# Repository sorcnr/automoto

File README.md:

# AutoMoto — Akıllı Motosiklet Telemetri, Güvenlik ve Keyless Go Sistemi

AutoMoto; ESP32-S3 mimarisi, SIMCom SIM808 GSM/GPRS + GPS hücresel modülü, BLE 5.0 yakınlık algılaması (Keyless Go) ve otomotiv sınıfı katı-hal (`PROFET` / `SSR`) anahtarlama teknolojisine dayanan yeni nesil bir akıllı motosiklet telemetri ve güvenlik platformudur.

## Proje ve Tasarım Dokümantasyonu

* **Proje Genel Tanımı ve Sistem Mimarisi:** [PROJECT.md](file:///home/sorcnr/Documents/automoto/PROJECT.md)
* **PCB & Şematik Teknik İmalat Şartnamesi (v4.0):** [hardware/pcb/PCB_SPECIFICATION.md](file:///home/sorcnr/Documents/automoto/hardware/pcb/PCB_SPECIFICATION.md)

---

## Donanım ve CAD Dosyaları (`hardware/pcb/`)

* **KiCad 10 Elektrik Şematik:** [hardware/pcb/automoto.kicad_sch](file:///home/sorcnr/Documents/automoto/hardware/pcb/automoto.kicad_sch)
* **KiCad 10 4-Katmanlı PCB:** [hardware/pcb/automoto.kicad_pcb](file:///home/sorcnr/Documents/automoto/hardware/pcb/automoto.kicad_pcb)
* **Özel Sembol Kütüphanesi:** [hardware/pcb/automoto.kicad_sym](file:///home/sorcnr/Documents/automoto/hardware/pcb/automoto.kicad_sym)
* **Şematik ve PCB Üreteç Betikleri:**
  * [hardware/pcb/generate_kicad_sch.py](file:///home/sorcnr/Documents/automoto/hardware/pcb/generate_kicad_sch.py)
  * [hardware/pcb/generate_kicad_pcb.py](file:///home/sorcnr/Documents/automoto/hardware/pcb/generate_kicad_pcb.py)
* **Doğrulama Raporları:**
  * [hardware/pcb/erc_report.rpt](file:///home/sorcnr/Documents/automoto/hardware/pcb/erc_report.rpt) (ERC: 0 Violations)
  * [hardware/pcb/drc_report.rpt](file:///home/sorcnr/Documents/automoto/hardware/pcb/drc_report.rpt) (DRC: 0 Violations, 0 Unconnected Pads)

### Görsel Çıktılar

* **Şematik Çizimi:** [hardware/pcb/drawings/automoto_schematic.png](file:///home/sorcnr/Documents/automoto/hardware/pcb/drawings/automoto_schematic.png) | [PDF](file:///home/sorcnr/Documents/automoto/hardware/pcb/drawings/automoto_schematic.pdf)
* **2D PCB Yerleşimi:** [hardware/pcb/drawings/automoto_pcb.png](file:///home/sorcnr/Documents/automoto/hardware/pcb/drawings/automoto_pcb.png) | [SVG](file:///home/sorcnr/Documents/automoto/hardware/pcb/drawings/automoto_pcb.svg)
* **3D Raytracing Renderları:**
  * [hardware/pcb/renders/kicad_3d_isometric.png](file:///home/sorcnr/Documents/automoto/hardware/pcb/renders/kicad_3d_isometric.png)
  * [hardware/pcb/renders/kicad_3d_top.png](file:///home/sorcnr/Documents/automoto/hardware/pcb/renders/kicad_3d_top.png)
  * [hardware/pcb/renders/kicad_3d_bottom.png](file:///home/sorcnr/Documents/automoto/hardware/pcb/renders/kicad_3d_bottom.png)

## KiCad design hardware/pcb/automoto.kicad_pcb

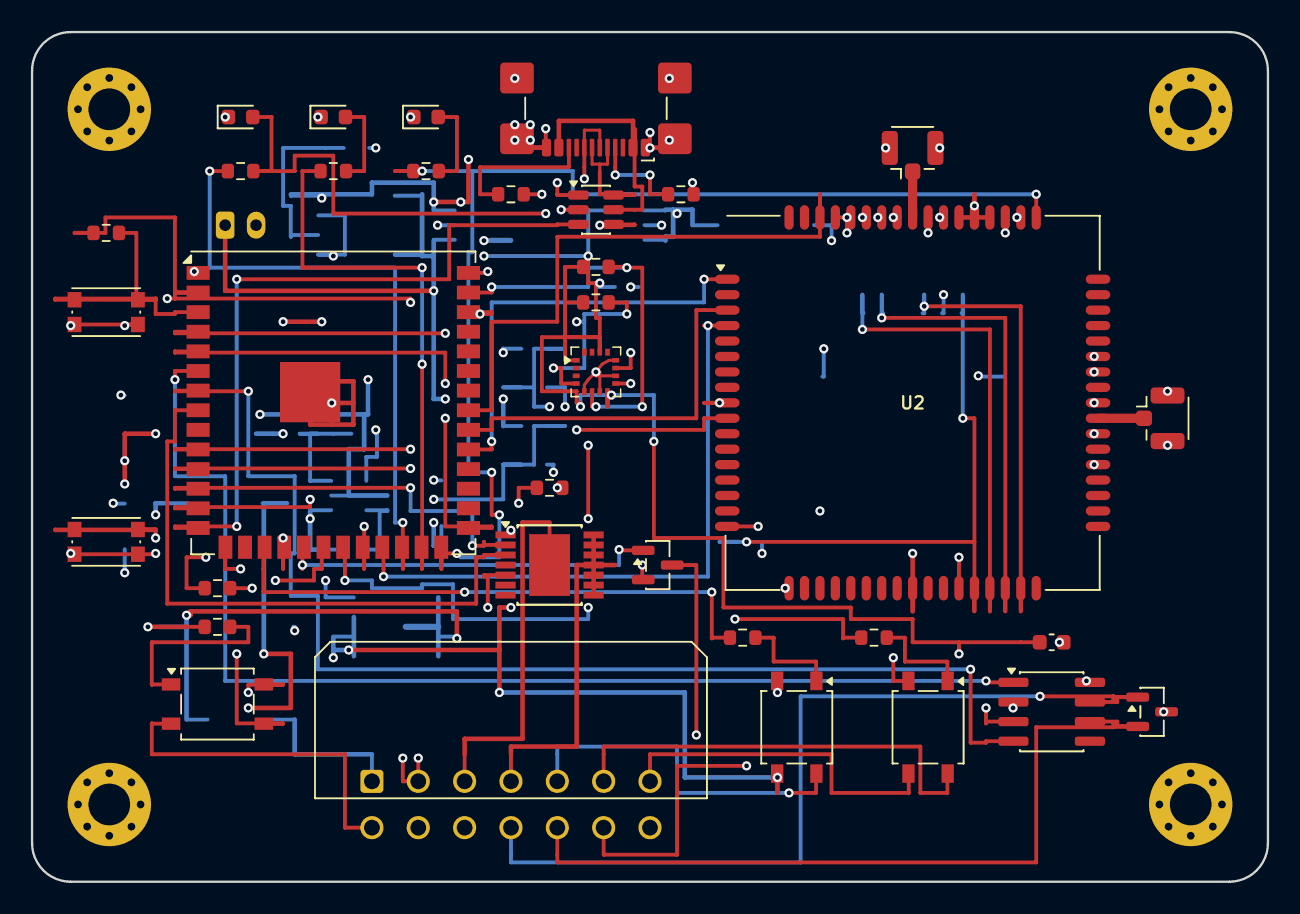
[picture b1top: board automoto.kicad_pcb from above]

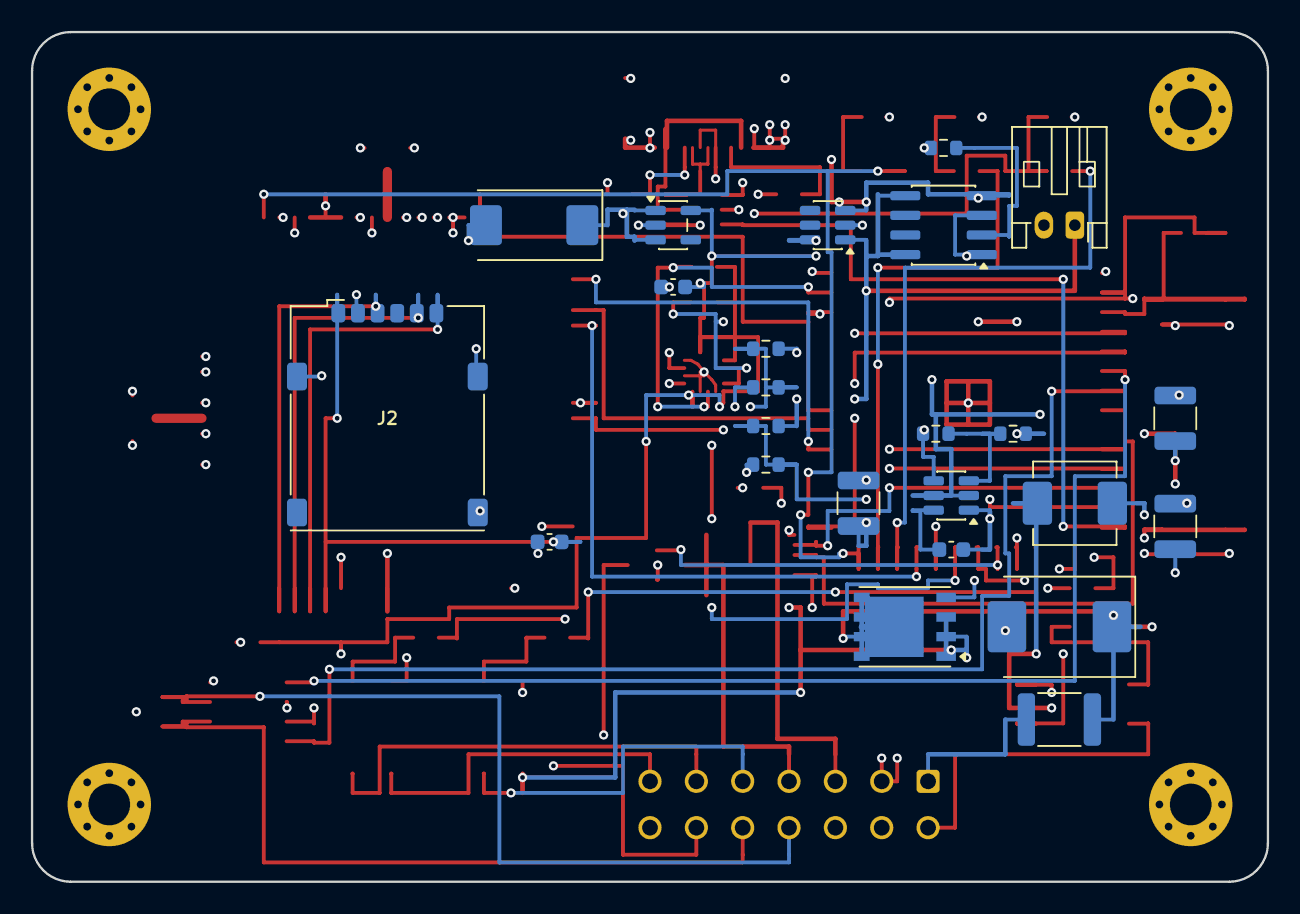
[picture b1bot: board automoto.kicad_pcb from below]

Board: 4 copper layers, 80.0 x 55.0 mm, 62 parts (24 on the bottom side), 65 nets.

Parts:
ANT1: GSM_UFL; U.FL_Hirose_U.FL-R-SMT-1_Vertical
ANT2: GPS_UFL; U.FL_Hirose_U.FL-R-SMT-1_Vertical
C1: 22uF_25V; C_1210_3225Metric
C2: 22uF_50V; C_1210_3225Metric
C3: 47uF_10V; C_1210_3225Metric
C4: 100uF_Tantal; CP_EIA-7343-31_Kemet-D
C5, C7, C8: 100nF; C_0603_1608Metric
C6: 10uF; C_0603_1608Metric
D1: TPSMC36A; D_SMC
D2: PESD2CAN; SOT-23
D3: USBLC6; SOT-23-6
F1: 1812L200PR; Fuse_1812_4532Metric
H1, H2, H3, H4: M2.5_Hole; MountingHole_2.7mm_M2.5_Pad_Via
J1: Molex_14P; Molex_Micro-Fit_3.0_43045-1400_2x07_P3.00mm_Horizontal
J2: Nano_SIM; nanoSIM_Hinged_CUI_NSIM-2-C
J3: JST_LiFePO4; JST_PH_S2B-PH-K_1x02_P2.00mm_Horizontal
J4: USB_C; USB_C_Receptacle_GCT_USB4110
L1: 6.8uH; L_Vishay_IHLP-2020
LED1: RED_ALARM; LED_0603_1608Metric
LED2: BLUE_BLE; LED_0603_1608Metric
LED3: GREEN_GSM; LED_0603_1608Metric
Q1: SQJ411EP; PowerPAK_SO-8_Single
Q5: DMN6075S; SOT-23
R1: 54.9k; R_0603_1608Metric
R2, R4, R14, R16: 10k; R_0603_1608Metric
R3: 2.4k; R_0603_1608Metric
R5, R6, R7, R11, R12: 330R; R_0603_1608Metric
R8, R9: 5.1k; R_0603_1608Metric
R10: 1.2k; R_0603_1608Metric
R13, R19, R20: 4.7k; R_0603_1608Metric
R15, R17, R18: 100k; R_0603_1608Metric
SW1: RESET; SW_Push_1P1T_NO_CK_KMR2
SW2: BOOT; SW_Push_1P1T_NO_CK_KMR2
U1: ESP32-S3-WROOM-1U
U2: SIMCom_SIM808; SIMCom_SIM900
U3: LIS3DH; LGA-16_3x3mm_P0.5mm
U4: TPS54302; SOT-23-6
U5: CN3058; SOIC-8_3.9x4.9mm_P1.27mm
U6: LM66100; SOT-23-6
U7: AP2112K-3.3; SOT-23-5
U8: SN65HVD230; SOIC-8_3.9x4.9mm_P1.27mm
U9: LTV-356T; SO-4_4.4x4.3mm_P2.54mm
U10: BTS7002-1EPP; Infineon_PG-TSDSO-14-22
U11: VO14642_Start; SO-4_4.4x4.3mm_P2.54mm
U12: VO14642_Kill; SO-4_4.4x4.3mm_P2.54mm

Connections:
+3V3: C6.1, C8.1, R4.1, R19.1, R20.1, U1.2, U3.1, U3.8, U3.14, U7.5, U8.3, U9.4
+12V_IN: C2.1, J1.9, Q1.1, Q1.2, Q1.3, R13.1, R15.1, U4.2, U4.5, U11.3
+12V_PROT: D1.1, F1.2, Q1.5
+12V_RAW: F1.1, J1.1
ADC_VBAT_BIKE: R15.2, R16.1, U1.21
ADC_VBAT_INT: R17.2, R18.1, U1.22
BUCK_BOOT: C5.2, U4.6
BUCK_FB: R1.2, R2.1, U4.3
BUCK_SW: C5.1, L1.1, U4.1
CAN_H: D2.1, J1.11, U8.7
CAN_L: D2.2, J1.12, U8.6
CAN_RX: U1.7, U8.4
CAN_TX: U1.6, U8.1
CHRG_ISET: R3.1, U5.2
ESP_BOOT: SW2.1, U1.27
ESP_EN: R4.2, SW1.1, U1.3
GND: ANT1.2, ANT2.2, C1.2, C2.2, C3.2, C4.2, C6.2, C7.2, C8.2, D1.2, D2.3, D3.2, H1.1, H2.1, H3.1, H4.1, J1.2, J1.14, J2.5, J2.SH, J3.2, J4.A1, J4.A12, J4.B1, J4.B12, J4.SH, LED1.1, LED2.1, LED3.1, Q1.4, Q5.2, R2.2, R3.2, R8.2, R9.2, R10.2, R14.2, R16.2, R18.2, SW1.2, SW2.2, U1.1, U1.40, U1.41, U2.17, U2.18, U2.29, U2.39, U2.41, U2.43, U2.45, U2.46, U2.53, U2.54, U2.58, U2.59, U2.61, U2.62, U2.63, U2.64, U2.65, U3.5, U3.7, U3.10, U3.12, U4.4, U5.1, U5.3, U6.2, U7.2, U8.2, U8.8, U10.1, U11.2, U12.2
GSM_DTR: U1.32, U2.3
GSM_PWRKEY: U1.31, U2.1
GSM_RI: U1.23, U2.4
GSM_RXD: U1.10, U2.10
GSM_STATUS: U1.33, U2.66
GSM_TXD: U1.11, U2.9
I2C_SCL: R19.2, U1.38, U3.4
I2C_SDA: R20.2, U1.39, U3.6
IGNITION_IN: J1.3, U10.15
IGNITION_OUT: J1.4, U10.8, U10.9, U10.10, U10.11, U10.12, U10.13, U10.14
IMU_INT1: U1.4, U3.11
IMU_INT2: U1.5, U3.9
KILL_SWITCH_A: J1.6, U12.4
KILL_SWITCH_B: J1.7, U12.3
LED1_A: J1.13, LED1.2, R5.2
LED2_A: LED2.2, R6.2
LED3_A: LED3.2, R7.2
LED_ALARM_DRV: R5.1, U1.24
LED_BLE_DRV: R6.1, U1.25
LED_GSM_DRV: R7.1, U1.26, U2.52
NEUTRAL_ANODE: R13.2, U9.1
NEUTRAL_OUT: R14.1, U1.20, U9.3
NEUTRAL_SENSE: J1.8, U9.2
PROFET_DEN: U1.8, U10.3
PROFET_IN: U1.12, U10.2
PROFET_IS: R10.1, U1.18, U10.5
RF_GPS: ANT2.1, U2.42
RF_GSM: ANT1.1, U2.60
SIM_CLK: J2.3, U2.32
SIM_DATA: J2.7, U2.31
SIM_RST: J2.2, U2.33
SIM_VDD: C7.1, J2.1, U2.30
SIREN_DRV: Q5.1, U1.19
SIREN_NEG: J1.10, Q5.3
SSR1_A: R11.2, U11.1
SSR2_A: R12.2, U12.1
SSR_KILL_DRV: R12.1, U1.15
SSR_STARTER_DRV: R11.1, U1.17
STARTER_CTRL: J1.5, U11.4
USB_CC1: J4.A5, R8.1
USB_CC2: J4.B5, R9.1
USB_CON_DN: D3.6, J4.A7, J4.B7
USB_CON_DP: D3.4, J4.A6, J4.B6
USB_DN: D3.1, U1.13
USB_DP: D3.3, U1.14
VBAT_LIFEPO4: J3.1, R17.1, U5.5, U5.8, U6.1
VBUS_5V: D3.5, J4.A4, J4.A9, J4.B4, J4.B9
VSYS_3V86: C1.1, C3.1, C4.1, L1.2, R1.1, U2.26, U2.55, U2.56, U2.57, U5.4, U6.3, U6.6, U7.1, U7.3

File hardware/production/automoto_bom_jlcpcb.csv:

Comment,Designator,Footprint,LCSC Part #,Manufacturer,Package,Description,DNP
ESP32-S3-WROOM-1U-N16R8,U1,SMD Modül (18.0x19.2 mm),C2913204,Espressif Systems,SMD Module,"Dual-Core 240MHz MCU, 16MB Flash, 8MB PSRAM, BLE 5.0, U.FL",NO
SIM808,U2,LCC-68 (24.0x24.0 mm),C126275,SIMCom Wireless,LCC-68,Quad-Band GSM/GPRS + GPS/GNSS Modülü,NO
LIS3DHTR,U3,LGA-16 (3.0x3.0 mm),C71933,STMicroelectronics,LGA-16,3-Eksen Ultra Düşük Güç Tüketimli MEMS İvmeölçer,NO
TPS54302DDCR,U4,SOT-23-6,C93121,Texas Instruments,SOT-23-6,"4.5V-28V Giriş, 3.86V 3A Senkron Step-Down Buck Regülatör",NO
CN3058E,U5,SOIC-8-EP,C112011,Consonance Elec,SOIC-8-EP,3.2V LiFePO4 Özel Şarj Yönetim Entegresi (3.65V Kesme),NO
LM66100DCKR,U6,SC-70-6,C2869734,Texas Instruments,SC-70-6,1.5A Kesintisiz Güç Yolu İdeal Diyot,NO
AP2112K-3.3TRG1,U7,SOT-23-5,C228383,Diodes Inc.,SOT-23-5,3.3V 600mA Düşük Gürültülü LDO Regülatör,NO
SN65HVD230DR,U8,SOIC-8,C12084,Texas Instruments,SOIC-8,3.3V CAN-Bus Alıcı-Verici (1 Mbps),NO
LTV-356T,U9,SOP-4,C1709,Lite-On,SOP-4,3.75 kVrms Optokuplör (Boş Vites Müşür İzolasyonu),NO
BTS7002-1EPP,U10,PG-TSDSO-14-22,C534824,Infineon Technologies,PG-TSDSO-14,2.6 mΩ 21A Akıllı Yüksek Taraf PROFET Anahtarı + Akım Algılama,NO
VO14642AABTR,"U11, U12",SOP-4,C2653901,Vishay,SOP-4,Opto-MOSFET Solid-State Röle 60V 2A (Marş & Kill-Switch),NO
SQJ411EP,Q1,PowerPAK SO-8,C2681534,Vishay,PowerPAK SO-8,P-Kanal -40V 30A Ters Polarite Koruma MOSFET,NO
DMN6075S,Q5,SOT-23,C209633,Diodes Inc.,SOT-23,N-Kanal 60V 2.5A 110 dB Siren Sürücü MOSFET,NO
TPSMC36A,D1,DO-214AB (SMC),C343277,Littelfuse,SMC,1500W Otomotiv Geçici Gerilim Bastırıcı TVS Diyot,NO
PESD2CAN,D2,SOT-23,C35282,Nexperia,SOT-23,CAN-Bus Çift Yönlü ESD Koruma Diyotu,NO
USBLC6-2SC6,D3,SOT-23-6,C7519,STMicroelectronics,SOT-23-6,USB Type-C D+/D-/VBUS ESD Koruma Entegresi,NO
1812L200PR,F1,SMD 1812,C70154,Littelfuse,1812,2A Tutma / 4A Atma PTC Polimer Sigorta,NO
6.8uH (IHLP-2020),L1,SMD 5.2x5.2 mm,C167732,Vishay / Sunlord,SMD 5.2x5.2,6.8 µH Korumalı Güç Bobini (4.5A Doyum),NO
22uF 50V X7R,"C1, C2",SMD 1210,C15850,Murata / Yageo,1210,Buck Giriş Filtre Seramik Kapasitörleri,NO
47uF 10V X7R,C3,SMD 1210,C96985,Murata / Yageo,1210,Buck Çıkış Filtre Seramik Kapasitörü,NO
100uF 10V Tantal,C4,EIA-7343-31 (D Kılıf),C7171,AVX / KEMET,7343,SIM808 2A GSM RF Burst Tepe Akım Tampon Tantal,NO
100nF 50V X7R,"C5, C7, C8",SMD 0603,C14663,Yageo,0603,BOOT & RF Dekuplaj Kapasitörleri,NO
10uF 16V X7R,C6,SMD 0603,C19702,Yageo,0603,3.3V LDO Çıkış Filtre Kapasitörü,NO
330R 1%,"R5, R6, R7, R11, R12",SMD 0603,C23140,Uniroyal / Yageo,0603,LED ve SSR Sürücü Akım Sınırlama Dirençleri,NO
10k 1%,"R2, R4, R14, R16",SMD 0603,C25804,Uniroyal / Yageo,0603,Pull-Up / Gerilim Bölücü Dirençleri,NO
4.7k 1%,"R13, R19, R20",SMD 0603,C23162,Uniroyal / Yageo,0603,PWRKEY & Sinyal Seri/Pull-Up Dirençleri,NO
100k 1%,"R15, R17, R18",SMD 0603,C25803,Uniroyal / Yageo,0603,Buck Gerilim Bölücü & Bias Dirençleri,NO
5.1k 1%,"R8, R9",SMD 0603,C23186,Uniroyal / Yageo,0603,USB Type-C CC1/CC2 Pull-Down Dirençleri,NO
1.2k 1%,R10,SMD 0603,C22775,Uniroyal / Yageo,0603,BTS7002 IS Akım Algılama Şönt Direnci,NO
54.9k 1%,R1,SMD 0603,C23214,Uniroyal / Yageo,0603,Giriş Gerilim Algılama Bölücü Direnci,NO
2.4k 1%,R3,SMD 0603,C23089,Uniroyal / Yageo,0603,LiFePO4 Şarj Akım Programlama Direnci,NO
RED LED,LED1,SMD 0603,C2286,Everlight,0603,Kırmızı Alarm Durum LED'i,NO
BLUE LED,LED2,SMD 0603,C72041,Everlight,0603,Mavi BLE Durum LED'i,NO
GREEN LED,LED3,SMD 0603,C72043,Everlight,0603,Yeşil GSM/Hücresel Durum LED'i,NO
SMD Push Button,"SW1, SW2",SMD 5x5mm (KMR2),C318884,C&K / Korean HRO,SMD 4P,Reset (SW1) & Bootloader (SW2) Butonları,NO
Nano SIM Socket,J2,SMD Push-Pull,C383794,Korean HRO,SMD 6P,Alt Yüzey Nano SIM Kart Yuvası,NO
USB Type-C 16-Pin,J4,SMD USB-C,C2765186,GCT / Korean HRO,SMD 16P,Yerel Seri Programlama ve Telemetri Portu,NO
U.FL-R-SMT-1,"ANT1, ANT2",SMD 3x3mm,C14899,Hirose / LCSC,SMD,GSM & GPS Harici Anten Konnektörleri,NO
Molex Micro-Fit 14P (43045-1400),J1,Through-Hole 2x7 R/A P3.0mm,DNF (Do Not Fit - Hand Soldered),Molex,Through-Hole,Ana Araç Tesisat Soketi (Geliştirici tarafından el ile lehimlenecektir),YES
JST-PH 2-Pin,J3,Through-Hole R/A P2.0mm,DNF (Do Not Fit - Hand Soldered),JST,Through-Hole,LiFePO4 Batarya Soketi (El ile lehimlenecektir),YES
M2.5 Mounting Hole,"H1, H2, H3, H4",M2.5 Pad Via,DNF (Mechanical),Standard,Mechanical,Şase ve Kutu Sabitleme Montaj Delikleri,YES

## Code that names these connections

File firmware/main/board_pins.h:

#ifndef BOARD_PINS_H
#define BOARD_PINS_H

#include <stdint.h>
#include <stdbool.h>
#include "driver/gpio.h"
#include "esp_err.h"

#ifdef __cplusplus
extern "C" {
#endif

// ==============================================================================
// AutoMoto ESP32-S3-WROOM-1U Pin Eşleşmeleri (PCB v4.0 Spesifikasyonu)
// ==============================================================================

// I2C Veri Yolu (LIS3DH MEMS İvmeölçer)
#define PIN_I2C_SDA             GPIO_NUM_1
#define PIN_I2C_SCL             GPIO_NUM_2

// Katı-Hal Röleler ve Güç Anahtarları
#define PIN_SSR_KILL            GPIO_NUM_3   // U12: VO14642AAB Motor Ateşleme Kesici (Active HIGH)
#define PIN_PROFET_IN           GPIO_NUM_8   // U10: BTS7002-1EPP 25A Kontak Anahtarı (Active HIGH)
#define PIN_SSR_STARTER         GPIO_NUM_9   // U11: VO14642AAB Marş SSR (Active HIGH)
#define PIN_PROFET_DEN          GPIO_NUM_15  // U10: Teşhis Yetkilendirme (Diagnostic Enable)
#define PIN_PROFET_IS           GPIO_NUM_10  // U10: IS Akım Ölçüm Şöntü (ADC1_CHANNEL_9)

// Ses ve Emniyet Giriş/Çıkışları
#define PIN_SIREN_CTRL          GPIO_NUM_11  // Q5: DMN6075S N-FET 110 dB Siren Sürücüsü (Active HIGH)
#define PIN_SENSE_NEUTRAL       GPIO_NUM_12  // U9: LTV-356T Boş Vites Algılama (Active LOW)

// MEMS Sensör Kesme Hatları (LIS3DH)
#define PIN_IMU_INT1            GPIO_NUM_4   // Sarsıntı / Uyandırma Kesmesi
#define PIN_IMU_INT2            GPIO_NUM_5   // Kaza / Devrilme Algılama Kesmesi

// CAN-Bus (SN65HVD230 Alıcı-Verici)
#define PIN_CAN_TX              GPIO_NUM_6
#define PIN_CAN_RX              GPIO_NUM_7

// Hücresel Modem Arayüzü (SIM808 / Quectel EG915U UART & Kontrol)
#define PIN_MODEM_TX            GPIO_NUM_17  // ESP TX -> Modem RXD
#define PIN_MODEM_RX            GPIO_NUM_18  // ESP RX <- Modem TXD
#define PIN_MODEM_STATUS        GPIO_NUM_21  // Modem Açık Durum Girişi
#define PIN_MODEM_PWRKEY        GPIO_NUM_38  // Modem Açma/Kapama Pals Çıkışı

// Kullanıcı Bildirim LED'leri (Active HIGH)
#define PIN_LED_GSM             GPIO_NUM_46  // LED3 (Yeşil): GSM / Şebeke Durumu
#define PIN_LED_ALARM           GPIO_NUM_47  // LED1 (Kırmızı): Alarm / Sabotaj Durumu
#define PIN_LED_BLE             GPIO_NUM_48  // LED2 (Mavi): Keyless BLE Durumu

// Fonksiyon Prototipleri
esp_err_t board_pins_init(void);
void board_set_ignition(bool state);
void board_set_starter(bool state);
void board_set_siren(bool state);
void board_set_kill_ssr(bool state);
bool board_is_neutral(void);

#ifdef __cplusplus
}
#endif

#endif // BOARD_PINS_H

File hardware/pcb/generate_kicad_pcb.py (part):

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    # --------------------------------------------------------------------------
    # A. RF 50-OHM MİKROŞERİT HATLAR (DOĞRUDAN DÜZ HAT, 0 VIA)
    # --------------------------------------------------------------------------
    # 1. RF_GSM: U2 Pin 60 (57.0, 12.0) -> ANT1 Pad 1 (57.0, 9.025)
    router.add_manual_polyline([(57.0, 12.0), (57.0, 9.025)], 0.60, pcbnew.F_Cu, "RF_GSM")
    # 2. RF_GPS: U2 Pin 42 (69.0, 25.0) -> ANT2 Pad 1 (71.975, 25.0)
    router.add_manual_polyline([(69.0, 25.0), (71.975, 25.0)], 0.60, pcbnew.F_Cu, "RF_GPS")

    # --------------------------------------------------------------------------
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    router.add_manual_polyline([(2.75, 32.20), (6.85, 32.20)], 0.25, pcbnew.F_Cu, "ESP_BOOT")
    router.add_manual_polyline([(2.75, 33.80), (6.85, 33.80)], 0.25, pcbnew.F_Cu, "GND")

    # U10 (BTS7002-1EPP) Sağ Sıra Pin 8..14 (IGNITION_OUT) dikey bara (tam X=36.35mm!)
    router.add_manual_polyline([(36.35, 32.55), (36.35, 36.45)], 0.30, pcbnew.F_Cu, "IGNITION_OUT")

    # Q1 (SQJ411EP B.Cu): Sol sıra Pin 1,2,3 (X=20.83, Y=40.405..37.865) (+12V_IN)
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    router.add_manual_polyline([(34.50, 19.75), (34.50, 17.50), (35.675, 17.50)], 0.25, pcbnew.F_Cu, "+3V3")
    router.add_manual_polyline([(34.50, 17.50), (34.50, 15.20), (35.675, 15.20)], 0.25, pcbnew.F_Cu, "+3V3")

    # U2 (SIMCom SIM808 F.Cu): Pin 55 (62.0, 12.0), 56 (61.0, 12.0), 57 (60.0, 12.0) (VSYS_3V86) üst bara
    router.add_manual_polyline([(60.0, 12.0), (62.0, 12.0)], 0.30, pcbnew.F_Cu, "VSYS_3V86")

    # --------------------------------------------------------------------------
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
